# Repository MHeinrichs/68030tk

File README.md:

[This project moved to gitlab on the day M$ bought github](https://gitlab.com/MHeinrichs/68030tk)

The new repository is at: https://gitlab.com/MHeinrichs/68030tk

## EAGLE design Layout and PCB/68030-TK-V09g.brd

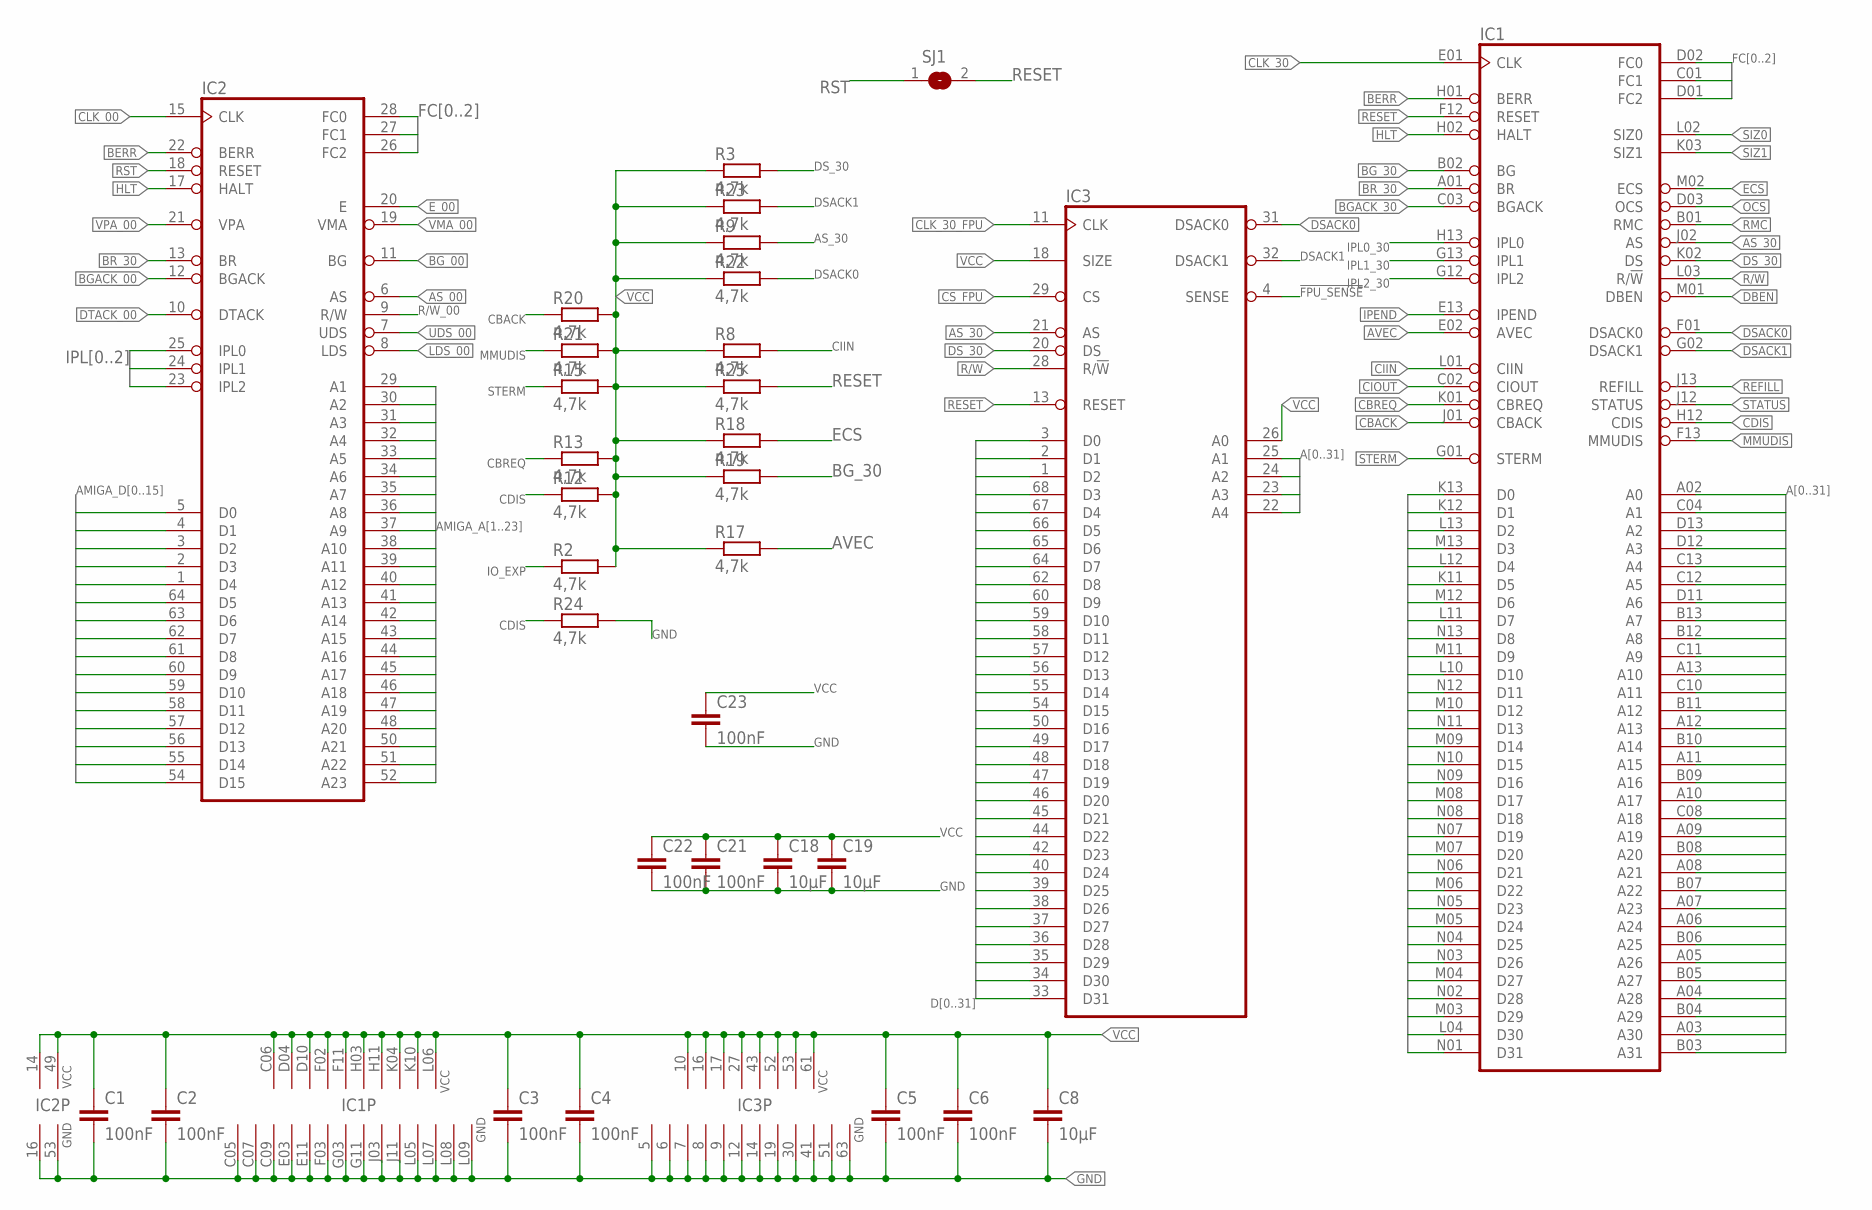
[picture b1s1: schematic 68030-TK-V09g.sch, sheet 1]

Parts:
C1, C2, C3, C4, C5, C6, C21, C22, C23: 100nF; C0603K
C8, C18, C19: 10µF; C1210
IC1: MC68030RC; MPGA128
IC2: MC68000P; DIL64
IC3: MC68881FN; PLCC68
R2, R3, R8, R9, R12, R13, R15, R17, R18, R19, R20, R21, R22, R23, R24, R25: 4,7k; R0603
SJ1: SJ

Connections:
!FPU_SENSE: IC3.4 (SENSE); also elsewhere on the board
A0: IC1.A02 (A0); also elsewhere on the board
A1: IC1.C04 (A1), IC3.25 (A1); also elsewhere on the board
A2: IC1.D13 (A2), IC3.24 (A2); also elsewhere on the board
A3: IC1.D12 (A3), IC3.23 (A3); also elsewhere on the board
A4: IC1.C13 (A4), IC3.22 (A4); also elsewhere on the board
A5: IC1.C12 (A5); also elsewhere on the board
A6: IC1.D11 (A6); also elsewhere on the board
A7: IC1.B13 (A7); also elsewhere on the board
A8: IC1.B12 (A8); also elsewhere on the board
A9: IC1.C11 (A9); also elsewhere on the board
A10: IC1.A13 (A10); also elsewhere on the board
A11: IC1.C10 (A11); also elsewhere on the board
A12: IC1.B11 (A12); also elsewhere on the board
A13: IC1.A12 (A13); also elsewhere on the board
A14: IC1.B10 (A14); also elsewhere on the board
A15: IC1.A11 (A15); also elsewhere on the board
A16: IC1.B09 (A16); also elsewhere on the board
A17: IC1.A10 (A17); also elsewhere on the board
A18: IC1.C08 (A18); also elsewhere on the board
A19: IC1.A09 (A19); also elsewhere on the board
A20: IC1.B08 (A20); also elsewhere on the board
A21: IC1.A08 (A21); also elsewhere on the board
A22: IC1.B07 (A22); also elsewhere on the board
A23: IC1.A07 (A23); also elsewhere on the board
A24: IC1.A06 (A24); also elsewhere on the board
A25: IC1.B06 (A25); also elsewhere on the board
A26: IC1.A05 (A26); also elsewhere on the board
A27: IC1.B05 (A27); also elsewhere on the board
A28: IC1.A04 (A28); also elsewhere on the board
A29: IC1.B04 (A29); also elsewhere on the board
A30: IC1.A03 (A30); also elsewhere on the board
A31: IC1.B03 (A31); also elsewhere on the board
AMIGA_A1: IC2.29 (A1); also elsewhere on the board
AMIGA_A2: IC2.30 (A2); also elsewhere on the board
AMIGA_A3: IC2.31 (A3); also elsewhere on the board
AMIGA_A4: IC2.32 (A4); also elsewhere on the board
AMIGA_A5: IC2.33 (A5); also elsewhere on the board
AMIGA_A6: IC2.34 (A6); also elsewhere on the board
AMIGA_A7: IC2.35 (A7); also elsewhere on the board
AMIGA_A8: IC2.36 (A8); also elsewhere on the board
AMIGA_A9: IC2.37 (A9); also elsewhere on the board
AMIGA_A10: IC2.38 (A10); also elsewhere on the board
AMIGA_A11: IC2.39 (A11); also elsewhere on the board
AMIGA_A12: IC2.40 (A12); also elsewhere on the board
AMIGA_A13: IC2.41 (A13); also elsewhere on the board
AMIGA_A14: IC2.42 (A14); also elsewhere on the board
AMIGA_A15: IC2.43 (A15); also elsewhere on the board
AMIGA_A16: IC2.44 (A16); also elsewhere on the board
AMIGA_A17: IC2.45 (A17); also elsewhere on the board
AMIGA_A18: IC2.46 (A18); also elsewhere on the board
AMIGA_A19: IC2.47 (A19); also elsewhere on the board
AMIGA_A20: IC2.48 (A20); also elsewhere on the board
AMIGA_A21: IC2.50 (A21); also elsewhere on the board
AMIGA_A22: IC2.51 (A22); also elsewhere on the board
AMIGA_A23: IC2.52 (A23); also elsewhere on the board
AMIGA_D0: IC2.5 (D0); also elsewhere on the board
AMIGA_D1: IC2.4 (D1); also elsewhere on the board
AMIGA_D2: IC2.3 (D2); also elsewhere on the board
AMIGA_D3: IC2.2 (D3); also elsewhere on the board
AMIGA_D4: IC2.1 (D4); also elsewhere on the board
AMIGA_D5: IC2.64 (D5); also elsewhere on the board
AMIGA_D6: IC2.63 (D6); also elsewhere on the board
AMIGA_D7: IC2.62 (D7); also elsewhere on the board
AMIGA_D8: IC2.61 (D8); also elsewhere on the board
AMIGA_D9: IC2.60 (D9); also elsewhere on the board
AMIGA_D10: IC2.59 (D10); also elsewhere on the board
AMIGA_D11: IC2.58 (D11); also elsewhere on the board
AMIGA_D12: IC2.57 (D12); also elsewhere on the board
AMIGA_D13: IC2.56 (D13); also elsewhere on the board
AMIGA_D14: IC2.55 (D14); also elsewhere on the board
AMIGA_D15: IC2.54 (D15); also elsewhere on the board
AS_00: IC2.6 (AS); also elsewhere on the board
AS_30: IC1.J02 (AS), IC3.21 (AS), R9.2; also elsewhere on the board
AVEC: IC1.E02 (AVEC), R17.2; also elsewhere on the board
BERR: IC1.H01 (BERR), IC2.22 (BERR); also elsewhere on the board
BGACK_00: IC2.12 (BGACK); also elsewhere on the board
BGACK_30: IC1.C03 (BGACK); also elsewhere on the board
BG_00: IC2.11 (BG); also elsewhere on the board
BG_30: IC1.B02 (BG), R19.2; also elsewhere on the board
BR_30: IC1.A01 (BR), IC2.13 (BR); also elsewhere on the board
CBACK: IC1.J01 (CBACK), R20.1; also elsewhere on the board
CBREQ: IC1.K01 (CBREQ), R13.1; also elsewhere on the board
CDIS: IC1.H12 (CDIS), R12.1, R24.1
CIIN: IC1.L01 (CIIN), R8.2; also elsewhere on the board
CIOUT: IC1.C02 (CIOUT)
CLK_00: IC2.15 (CLK); also elsewhere on the board
CLK_30: IC1.E01 (CLK); also elsewhere on the board
CLK_30_FPU: IC3.11 (CLK); also elsewhere on the board
CS_FPU: IC3.29 (CS); also elsewhere on the board
D0: IC1.K13 (D0), IC3.3 (D0); also elsewhere on the board
D1: IC1.K12 (D1), IC3.2 (D1); also elsewhere on the board
D2: IC1.L13 (D2), IC3.1 (D2); also elsewhere on the board
D3: IC1.M13 (D3), IC3.68 (D3); also elsewhere on the board
D4: IC1.L12 (D4), IC3.67 (D4); also elsewhere on the board
D5: IC1.K11 (D5), IC3.66 (D5); also elsewhere on the board
D6: IC1.M12 (D6), IC3.65 (D6); also elsewhere on the board
D7: IC1.L11 (D7), IC3.64 (D7); also elsewhere on the board
D8: IC1.N13 (D8), IC3.62 (D8); also elsewhere on the board
D9: IC1.M11 (D9), IC3.60 (D9); also elsewhere on the board
D10: IC1.L10 (D10), IC3.59 (D10); also elsewhere on the board
D11: IC1.N12 (D11), IC3.58 (D11); also elsewhere on the board
D12: IC1.M10 (D12), IC3.57 (D12); also elsewhere on the board
D13: IC1.N11 (D13), IC3.56 (D13); also elsewhere on the board
D14: IC1.M09 (D14), IC3.55 (D14); also elsewhere on the board
D15: IC1.N10 (D15), IC3.54 (D15); also elsewhere on the board
D16: IC1.N09 (D16), IC3.50 (D16); also elsewhere on the board
D17: IC1.M08 (D17), IC3.49 (D17); also elsewhere on the board
D18: IC1.N08 (D18), IC3.48 (D18); also elsewhere on the board
D19: IC1.N07 (D19), IC3.47 (D19); also elsewhere on the board
D20: IC1.M07 (D20), IC3.46 (D20); also elsewhere on the board
D21: IC1.N06 (D21), IC3.45 (D21); also elsewhere on the board
D22: IC1.M06 (D22), IC3.44 (D22); also elsewhere on the board
D23: IC1.N05 (D23), IC3.42 (D23); also elsewhere on the board
D24: IC1.M05 (D24), IC3.40 (D24); also elsewhere on the board
D25: IC1.N04 (D25), IC3.39 (D25); also elsewhere on the board
D26: IC1.N03 (D26), IC3.38 (D26); also elsewhere on the board
D27: IC1.M04 (D27), IC3.37 (D27); also elsewhere on the board
D28: IC1.N02 (D28), IC3.36 (D28); also elsewhere on the board
D29: IC1.M03 (D29), IC3.35 (D29); also elsewhere on the board
D30: IC1.L04 (D30), IC3.34 (D30); also elsewhere on the board
D31: IC1.N01 (D31), IC3.33 (D31); also elsewhere on the board
DBEN: IC1.M01 (DBEN)
DSACK0: IC1.F01 (DSACK0), IC3.31 (DSACK0), R22.2; also elsewhere on the board
DSACK1: IC1.G02 (DSACK1), IC3.32 (DSACK1), R23.2; also elsewhere on the board
DS_30: IC1.K02 (DS), IC3.20 (DS), R3.2; also elsewhere on the board
DTACK_00: IC2.10 (DTACK); also elsewhere on the board
ECS: IC1.M02 (ECS), R18.2; also elsewhere on the board
E_00: IC2.20 (E); also elsewhere on the board
FC0: IC1.D02 (FC0), IC2.28 (FC0); also elsewhere on the board
FC1: IC1.C01 (FC1), IC2.27 (FC1); also elsewhere on the board
FC2: IC1.D01 (FC2), IC2.26 (FC2); also elsewhere on the board
GND: C1.2, C2.2, C3.2, C4.2, C5.2, C6.2, C8.2, C18.2, C19.2, C21.2, C22.2, C23.2, IC1.C05 (GND), IC1.C07 (GND), IC1.C09 (GND), IC1.E03 (GND), IC1.E11 (GND), IC1.F03 (GND), IC1.G03 (GND), IC1.G11 (GND), IC1.J03 (GND), IC1.J11 (GND), IC1.L05 (GND), IC1.L07 (GND), IC1.L08 (GND), IC1.L09 (GND), IC2.16 (GND), IC2.53 (GND), IC3.5 (GND), IC3.6 (GND), IC3.7 (GND), IC3.8 (GND), IC3.9 (GND), IC3.12 (GND), IC3.14 (GND), IC3.19 (GND), IC3.30 (GND), IC3.41 (GND), IC3.51 (GND), IC3.63 (GND), R24.2; also elsewhere on the board
HLT: IC1.H02 (HALT), IC2.17 (HALT)
IO_EXP: R2.1; also elsewhere on the board
IPEND: IC1.E13 (IPEND)
IPL0: IC2.25 (IPL0); also elsewhere on the board
IPL0_30: IC1.H13 (IPL0); also elsewhere on the board
IPL1: IC2.24 (IPL1); also elsewhere on the board
IPL1_30: IC1.G13 (IPL1); also elsewhere on the board
IPL2: IC2.23 (IPL2); also elsewhere on the board
IPL2_30: IC1.G12 (IPL2); also elsewhere on the board
LDS_00: IC2.8 (LDS); also elsewhere on the board
MMUDIS: IC1.F13 (MMUDIS), R21.1
OCS: IC1.D03 (OCS)
R/W: IC1.L03 (R/!W), IC3.28 (R/!W); also elsewhere on the board
R/W_00: IC2.9 (R/W); also elsewhere on the board
REFILL: IC1.J13 (REFILL)
RESET: IC1.F12 (RESET), IC3.13 (RESET), R25.2, SJ1.2; also elsewhere on the board
RMC: IC1.B01 (RMC)
RST: IC2.18 (RESET), SJ1.1; also elsewhere on the board
SIZ0: IC1.L02 (SIZ0); also elsewhere on the board
SIZ1: IC1.K03 (SIZ1); also elsewhere on the board
STATUS: IC1.J12 (STATUS)
STERM: IC1.G01 (STERM), R15.1; also elsewhere on the board
UDS_00: IC2.7 (UDS); also elsewhere on the board
VCC: C1.1, C2.1, C3.1, C4.1, C5.1, C6.1, C8.1, C18.1, C19.1, C21.1, C22.1, C23.1, IC1.C06 (VCC), IC1.D04 (VCC), IC1.D10 (VCC), IC1.F02 (VCC), IC1.F11 (VCC), IC1.H03 (VCC), IC1.H11 (VCC), IC1.K04 (VCC), IC1.K10 (VCC), IC1.L06 (VCC), IC2.14 (VCC), IC2.49 (VCC), IC3.10 (VCC), IC3.16 (VCC), IC3.17 (VCC), IC3.18 (SIZE), IC3.26 (A0), IC3.27 (VCC), IC3.43 (VCC), IC3.52 (VCC), IC3.53 (VCC), IC3.61 (VCC), R2.2, R3.1, R8.1, R9.1, R12.2, R13.2, R15.2, R17.1, R18.1, R19.1, R20.2, R21.2, R22.1, R23.1, R25.1; also elsewhere on the board
VMA_00: IC2.19 (VMA); also elsewhere on the board
VPA_00: IC2.21 (VPA); also elsewhere on the board

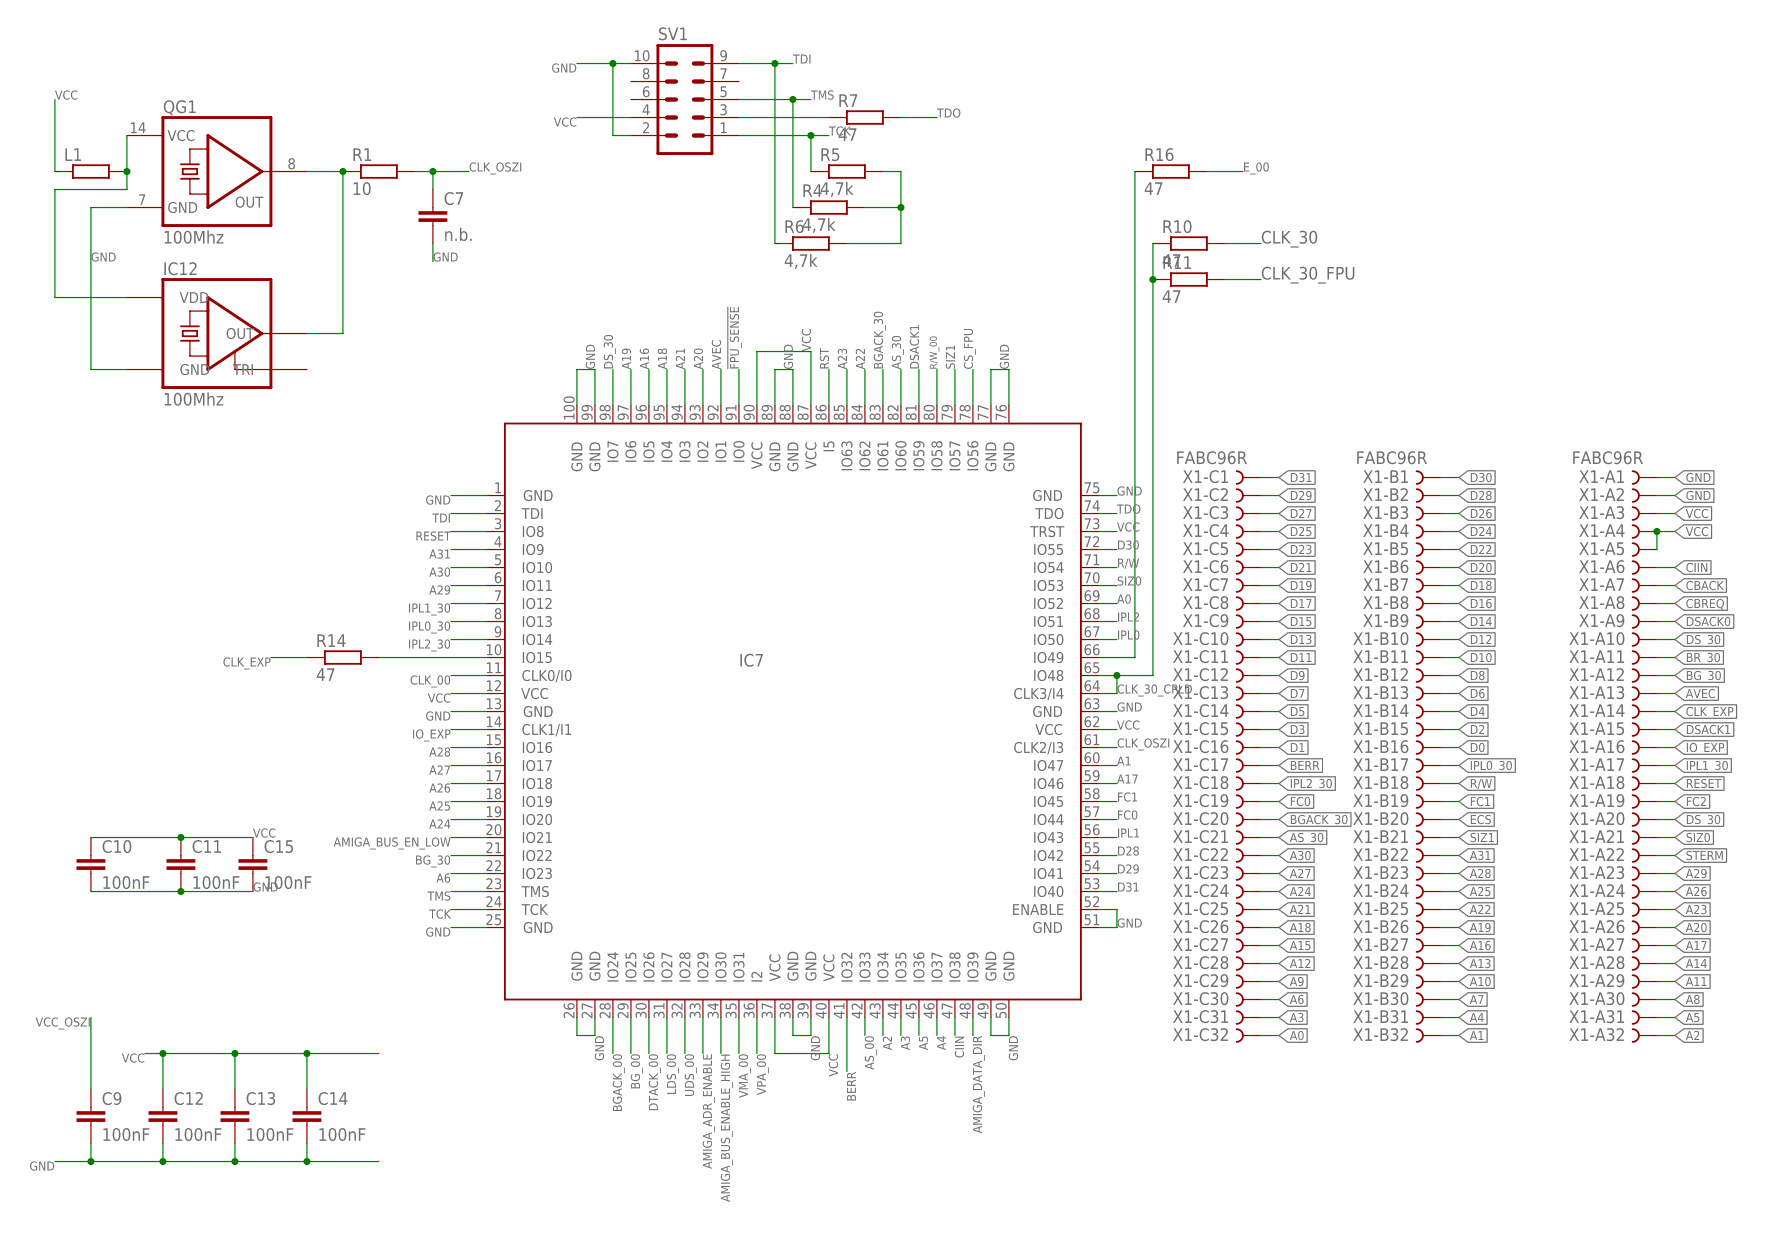
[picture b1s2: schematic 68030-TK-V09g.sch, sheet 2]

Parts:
C7: n.b.; C0805K
C9, C10, C11, C12, C13, C14, C15: 100nF; C0603K
IC7: M4-128T100; TQFP100
IC12: 100Mhz; 7X5
L1: R-EU_R0805; R0805
QG1: 100Mhz; DIL14S
R1: 10; R0805
R4, R5, R6: 4,7k; R0603
R7, R10, R11, R14, R16: 47; R0603
SV1: ML10
X1: FABC96R

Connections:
!FPU_SENSE: IC7.91 (IO0); also elsewhere on the board
A0: IC7.69 (IO52), X1.C32; also elsewhere on the board
A1: IC7.60 (IO47), X1.B32; also elsewhere on the board
A2: IC7.43 (IO34), X1.A32; also elsewhere on the board
A3: IC7.44 (IO35), X1.C31; also elsewhere on the board
A4: IC7.46 (IO37), X1.B31; also elsewhere on the board
A5: IC7.45 (IO36), X1.A31; also elsewhere on the board
A6: IC7.22 (IO23), X1.C30; also elsewhere on the board
A7: X1.B30; also elsewhere on the board
A8: X1.A30; also elsewhere on the board
A9: X1.C29; also elsewhere on the board
A10: X1.B29; also elsewhere on the board
A11: X1.A29; also elsewhere on the board
A12: X1.C28; also elsewhere on the board
A13: X1.B28; also elsewhere on the board
A14: X1.A28; also elsewhere on the board
A15: X1.C27; also elsewhere on the board
A16: IC7.96 (IO5), X1.B27; also elsewhere on the board
A17: IC7.59 (IO46), X1.A27; also elsewhere on the board
A18: IC7.95 (IO4), X1.C26; also elsewhere on the board
A19: IC7.97 (IO6), X1.B26; also elsewhere on the board
A20: IC7.93 (IO2), X1.A26; also elsewhere on the board
A21: IC7.94 (IO3), X1.C25; also elsewhere on the board
A22: IC7.84 (IO62), X1.B25; also elsewhere on the board
A23: IC7.85 (IO63), X1.A25; also elsewhere on the board
A24: IC7.19 (IO20), X1.C24; also elsewhere on the board
A25: IC7.18 (IO19), X1.B24; also elsewhere on the board
A26: IC7.17 (IO18), X1.A24; also elsewhere on the board
A27: IC7.16 (IO17), X1.C23; also elsewhere on the board
A28: IC7.15 (IO16), X1.B23; also elsewhere on the board
A29: IC7.6 (IO11), X1.A23; also elsewhere on the board
A30: IC7.5 (IO10), X1.C22; also elsewhere on the board
A31: IC7.4 (IO9), X1.B22; also elsewhere on the board
AMIGA_ADR_ENABLE: IC7.33 (IO29); also elsewhere on the board
AMIGA_BUS_ENABLE_HIGH: IC7.34 (IO30); also elsewhere on the board
AMIGA_BUS_EN_LOW: IC7.20 (IO21); also elsewhere on the board
AMIGA_DATA_DIR: IC7.48 (IO39); also elsewhere on the board
AS_00: IC7.42 (IO33); also elsewhere on the board
AS_30: IC7.82 (IO60), X1.C21; also elsewhere on the board
AVEC: IC7.92 (IO1), X1.A13; also elsewhere on the board
BERR: IC7.41 (IO32), X1.C17; also elsewhere on the board
BGACK_00: IC7.28 (IO24); also elsewhere on the board
BGACK_30: IC7.83 (IO61), X1.C20; also elsewhere on the board
BG_00: IC7.29 (IO25); also elsewhere on the board
BG_30: IC7.21 (IO22), X1.A12; also elsewhere on the board
BR_30: X1.A11; also elsewhere on the board
CBACK: X1.A7; also elsewhere on the board
CBREQ: X1.A8; also elsewhere on the board
CIIN: IC7.47 (IO38), X1.A6; also elsewhere on the board
CLK_00: IC7.11 (CLK0/I0); also elsewhere on the board
CLK_30: R10.2; also elsewhere on the board
CLK_30_CPLD: IC7.64 (CLK3/I4), IC7.65 (IO48), R10.1, R11.1
CLK_30_FPU: R11.2; also elsewhere on the board
CLK_EXP: R14.1, X1.A14
CLK_OSZI: C7.1, IC7.61 (CLK2/I3), R1.2
CS_FPU: IC7.78 (IO56); also elsewhere on the board
D0: X1.B16; also elsewhere on the board
D1: X1.C16; also elsewhere on the board
D2: X1.B15; also elsewhere on the board
D3: X1.C15; also elsewhere on the board
D4: X1.B14; also elsewhere on the board
D5: X1.C14; also elsewhere on the board
D6: X1.B13; also elsewhere on the board
D7: X1.C13; also elsewhere on the board
D8: X1.B12; also elsewhere on the board
D9: X1.C12; also elsewhere on the board
D10: X1.B11; also elsewhere on the board
D11: X1.C11; also elsewhere on the board
D12: X1.B10; also elsewhere on the board
D13: X1.C10; also elsewhere on the board
D14: X1.B9; also elsewhere on the board
D15: X1.C9; also elsewhere on the board
D16: X1.B8; also elsewhere on the board
D17: X1.C8; also elsewhere on the board
D18: X1.B7; also elsewhere on the board
D19: X1.C7; also elsewhere on the board
D20: X1.B6; also elsewhere on the board
D21: X1.C6; also elsewhere on the board
D22: X1.B5; also elsewhere on the board
D23: X1.C5; also elsewhere on the board
D24: X1.B4; also elsewhere on the board
D25: X1.C4; also elsewhere on the board
D26: X1.B3; also elsewhere on the board
D27: X1.C3; also elsewhere on the board
D28: IC7.55 (IO42), X1.B2; also elsewhere on the board
D29: IC7.54 (IO41), X1.C2; also elsewhere on the board
D30: IC7.72 (IO55), X1.B1; also elsewhere on the board
D31: IC7.53 (IO40), X1.C1; also elsewhere on the board
DSACK0: X1.A9; also elsewhere on the board
DSACK1: IC7.81 (IO59), X1.A15; also elsewhere on the board
DS_30: IC7.98 (IO7), X1.A10, X1.A20; also elsewhere on the board
DTACK_00: IC7.30 (IO26); also elsewhere on the board
ECS: X1.B20; also elsewhere on the board
E_00: R16.2; also elsewhere on the board
FC0: IC7.57 (IO44), X1.C19; also elsewhere on the board
FC1: IC7.58 (IO45), X1.B19; also elsewhere on the board
FC2: X1.A19; also elsewhere on the board
GND: C7.2, C9.2, C10.2, C11.2, C12.2, C13.2, C14.2, C15.2, IC7.1 (GND), IC7.13 (GND), IC7.25 (GND), IC7.26 (GND), IC7.27 (GND), IC7.38 (GND), IC7.39 (GND), IC7.49 (GND), IC7.50 (GND), IC7.51 (GND), IC7.52 (ENABLE), IC7.63 (GND), IC7.75 (GND), IC7.76 (GND), IC7.77 (GND), IC7.88 (GND), IC7.89 (GND), IC7.99 (GND), IC7.100 (GND), IC12.P$2 (GND), QG1.7 (GND), SV1.2, SV1.10, X1.A1, X1.A2; also elsewhere on the board
IO_EXP: IC7.14 (CLK1/I1), X1.A16; also elsewhere on the board
IPL0: IC7.67 (IO50); also elsewhere on the board
IPL0_30: IC7.8 (IO13), X1.B17; also elsewhere on the board
IPL1: IC7.56 (IO43); also elsewhere on the board
IPL1_30: IC7.7 (IO12), X1.A17; also elsewhere on the board
IPL2: IC7.68 (IO51); also elsewhere on the board
IPL2_30: IC7.9 (IO14), X1.C18; also elsewhere on the board
LDS_00: IC7.31 (IO27); also elsewhere on the board
unnamed: IC7.10 (IO15), R14.2
unnamed: IC7.66 (IO49), R16.1
OSZI_OUT: IC12.P$3 (OUT), QG1.8 (OUT), R1.1
R/W: IC7.71 (IO54), X1.B18; also elsewhere on the board
R/W_00: IC7.80 (IO58); also elsewhere on the board
RESET: IC7.3 (IO8), X1.A18; also elsewhere on the board
RST: IC7.86 (I5); also elsewhere on the board
SIZ0: IC7.70 (IO53), X1.A21; also elsewhere on the board
SIZ1: IC7.79 (IO57), X1.B21; also elsewhere on the board
STERM: X1.A22; also elsewhere on the board
TCK: IC7.24 (TCK), R5.1, SV1.1
TDI: IC7.2 (TDI), R6.1, SV1.9
TDO: IC7.74 (TDO), R7.2
TDO-PIN: R7.1, SV1.3
TMS: IC7.23 (TMS), R4.1, SV1.5
UDS_00: IC7.32 (IO28); also elsewhere on the board
VCC: C10.1, C11.1, C12.1, C13.1, C14.1, C15.1, IC7.12 (VCC), IC7.37 (VCC), IC7.40 (VCC), IC7.62 (VCC), IC7.73 (TRST), IC7.87 (VCC), IC7.90 (VCC), L1.1, R4.2, R5.2, R6.2, SV1.4, X1.A3, X1.A4, X1.A5; also elsewhere on the board
VCC_OSZI: C9.1, IC12.P$4 (VDD), L1.2, QG1.14 (VCC)
VMA_00: IC7.35 (IO31); also elsewhere on the board
VPA_00: IC7.36 (I2); also elsewhere on the board

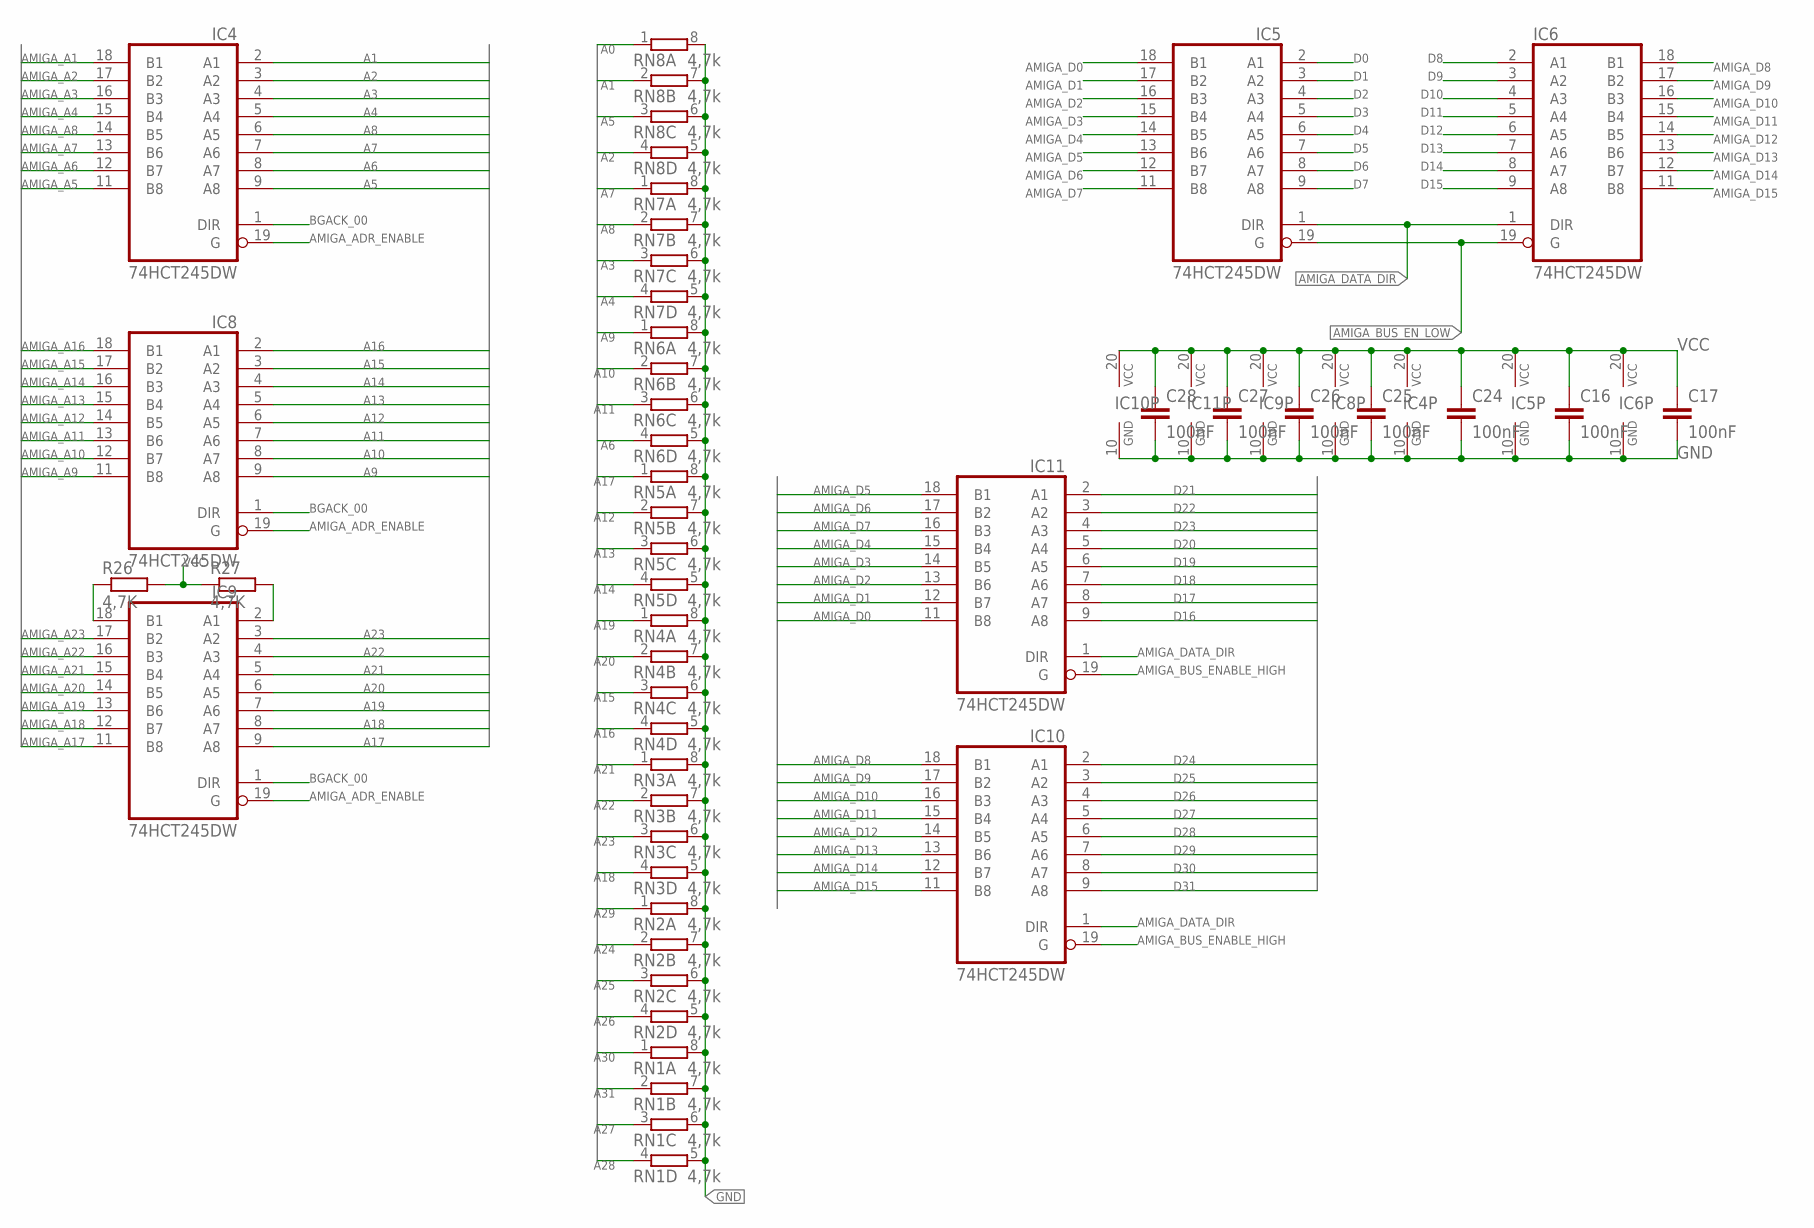
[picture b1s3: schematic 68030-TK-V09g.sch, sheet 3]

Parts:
C16, C17, C24, C25, C26, C27, C28: 100nF; C0603K
IC4, IC5, IC6, IC8, IC9, IC10, IC11: 74HCT245DW; SO20W
R26, R27: 4,7K; R0603
RN1, RN2, RN3, RN4, RN5, RN6, RN7, RN8: 4,7k; EXBV8V

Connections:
A0: RN8.1; also elsewhere on the board
A1: IC4.2 (A1), RN8.2 (1); also elsewhere on the board
A2: IC4.3 (A2), RN8.4 (1); also elsewhere on the board
A3: IC4.4 (A3), RN7.3 (1); also elsewhere on the board
A4: IC4.5 (A4), RN7.4 (1); also elsewhere on the board
A5: IC4.9 (A8), RN8.3 (1); also elsewhere on the board
A6: IC4.8 (A7), RN6.4 (1); also elsewhere on the board
A7: IC4.7 (A6), RN7.1; also elsewhere on the board
A8: IC4.6 (A5), RN7.2 (1); also elsewhere on the board
A9: IC8.9 (A8), RN6.1; also elsewhere on the board
A10: IC8.8 (A7), RN6.2 (1); also elsewhere on the board
A11: IC8.7 (A6), RN6.3 (1); also elsewhere on the board
A12: IC8.6 (A5), RN5.2 (1); also elsewhere on the board
A13: IC8.5 (A4), RN5.3 (1); also elsewhere on the board
A14: IC8.4 (A3), RN5.4 (1); also elsewhere on the board
A15: IC8.3 (A2), RN4.3 (1); also elsewhere on the board
A16: IC8.2 (A1), RN4.4 (1); also elsewhere on the board
A17: IC9.9 (A8), RN5.1; also elsewhere on the board
A18: IC9.8 (A7), RN3.4 (1); also elsewhere on the board
A19: IC9.7 (A6), RN4.1; also elsewhere on the board
A20: IC9.6 (A5), RN4.2 (1); also elsewhere on the board
A21: IC9.5 (A4), RN3.1; also elsewhere on the board
A22: IC9.4 (A3), RN3.2 (1); also elsewhere on the board
A23: IC9.3 (A2), RN3.3 (1); also elsewhere on the board
A24: RN2.2 (1); also elsewhere on the board
A25: RN2.3 (1); also elsewhere on the board
A26: RN2.4 (1); also elsewhere on the board
A27: RN1.3 (1); also elsewhere on the board
A28: RN1.4 (1); also elsewhere on the board
A29: RN2.1; also elsewhere on the board
A30: RN1.1; also elsewhere on the board
A31: RN1.2 (1); also elsewhere on the board
AMIGA_A1: IC4.18 (B1); also elsewhere on the board
AMIGA_A2: IC4.17 (B2); also elsewhere on the board
AMIGA_A3: IC4.16 (B3); also elsewhere on the board
AMIGA_A4: IC4.15 (B4); also elsewhere on the board
AMIGA_A5: IC4.11 (B8); also elsewhere on the board
AMIGA_A6: IC4.12 (B7); also elsewhere on the board
AMIGA_A7: IC4.13 (B6); also elsewhere on the board
AMIGA_A8: IC4.14 (B5); also elsewhere on the board
AMIGA_A9: IC8.11 (B8); also elsewhere on the board
AMIGA_A10: IC8.12 (B7); also elsewhere on the board
AMIGA_A11: IC8.13 (B6); also elsewhere on the board
AMIGA_A12: IC8.14 (B5); also elsewhere on the board
AMIGA_A13: IC8.15 (B4); also elsewhere on the board
AMIGA_A14: IC8.16 (B3); also elsewhere on the board
AMIGA_A15: IC8.17 (B2); also elsewhere on the board
AMIGA_A16: IC8.18 (B1); also elsewhere on the board
AMIGA_A17: IC9.11 (B8); also elsewhere on the board
AMIGA_A18: IC9.12 (B7); also elsewhere on the board
AMIGA_A19: IC9.13 (B6); also elsewhere on the board
AMIGA_A20: IC9.14 (B5); also elsewhere on the board
AMIGA_A21: IC9.15 (B4); also elsewhere on the board
AMIGA_A22: IC9.16 (B3); also elsewhere on the board
AMIGA_A23: IC9.17 (B2); also elsewhere on the board
AMIGA_ADR_ENABLE: IC4.19 (G), IC8.19 (G), IC9.19 (G); also elsewhere on the board
AMIGA_BUS_ENABLE_HIGH: IC10.19 (G), IC11.19 (G); also elsewhere on the board
AMIGA_BUS_EN_LOW: IC5.19 (G), IC6.19 (G); also elsewhere on the board
AMIGA_D0: IC5.18 (B1), IC11.11 (B8); also elsewhere on the board
AMIGA_D1: IC5.17 (B2), IC11.12 (B7); also elsewhere on the board
AMIGA_D2: IC5.16 (B3), IC11.13 (B6); also elsewhere on the board
AMIGA_D3: IC5.15 (B4), IC11.14 (B5); also elsewhere on the board
AMIGA_D4: IC5.14 (B5), IC11.15 (B4); also elsewhere on the board
AMIGA_D5: IC5.13 (B6), IC11.18 (B1); also elsewhere on the board
AMIGA_D6: IC5.12 (B7), IC11.17 (B2); also elsewhere on the board
AMIGA_D7: IC5.11 (B8), IC11.16 (B3); also elsewhere on the board
AMIGA_D8: IC6.18 (B1), IC10.18 (B1); also elsewhere on the board
AMIGA_D9: IC6.17 (B2), IC10.17 (B2); also elsewhere on the board
AMIGA_D10: IC6.16 (B3), IC10.16 (B3); also elsewhere on the board
AMIGA_D11: IC6.15 (B4), IC10.15 (B4); also elsewhere on the board
AMIGA_D12: IC6.14 (B5), IC10.14 (B5); also elsewhere on the board
AMIGA_D13: IC6.13 (B6), IC10.13 (B6); also elsewhere on the board
AMIGA_D14: IC6.12 (B7), IC10.12 (B7); also elsewhere on the board
AMIGA_D15: IC6.11 (B8), IC10.11 (B8); also elsewhere on the board
AMIGA_DATA_DIR: IC5.1 (DIR), IC6.1 (DIR), IC10.1 (DIR), IC11.1 (DIR); also elsewhere on the board
BGACK_00: IC4.1 (DIR), IC8.1 (DIR), IC9.1 (DIR); also elsewhere on the board
D0: IC5.2 (A1); also elsewhere on the board
D1: IC5.3 (A2); also elsewhere on the board
D2: IC5.4 (A3); also elsewhere on the board
D3: IC5.5 (A4); also elsewhere on the board
D4: IC5.6 (A5); also elsewhere on the board
D5: IC5.7 (A6); also elsewhere on the board
D6: IC5.8 (A7); also elsewhere on the board
D7: IC5.9 (A8); also elsewhere on the board
D8: IC6.2 (A1); also elsewhere on the board
D9: IC6.3 (A2); also elsewhere on the board
D10: IC6.4 (A3); also elsewhere on the board
D11: IC6.5 (A4); also elsewhere on the board
D12: IC6.6 (A5); also elsewhere on the board
D13: IC6.7 (A6); also elsewhere on the board
D14: IC6.8 (A7); also elsewhere on the board
D15: IC6.9 (A8); also elsewhere on the board
D16: IC11.9 (A8); also elsewhere on the board
D17: IC11.8 (A7); also elsewhere on the board
D18: IC11.7 (A6); also elsewhere on the board
D19: IC11.6 (A5); also elsewhere on the board
D20: IC11.5 (A4); also elsewhere on the board
D21: IC11.2 (A1); also elsewhere on the board
D22: IC11.3 (A2); also elsewhere on the board
D23: IC11.4 (A3); also elsewhere on the board
D24: IC10.2 (A1); also elsewhere on the board
D25: IC10.3 (A2); also elsewhere on the board
D26: IC10.4 (A3); also elsewhere on the board
D27: IC10.5 (A4); also elsewhere on the board
D28: IC10.6 (A5); also elsewhere on the board
D29: IC10.7 (A6); also elsewhere on the board
D30: IC10.8 (A7); also elsewhere on the board
D31: IC10.9 (A8); also elsewhere on the board
GND: C16.2, C17.2, C24.2, C25.2, C26.2, C27.2, C28.2, IC4.10 (GND), IC5.10 (GND), IC6.10 (GND), IC8.10 (GND), IC9.10 (GND), IC10.10 (GND), IC11.10 (GND), RN1.5 (2), RN1.6 (2), RN1.7 (2), RN1.8 (2), RN2.5 (2), RN2.6 (2), RN2.7 (2), RN2.8 (2), RN3.5 (2), RN3.6 (2), RN3.7 (2), RN3.8 (2), RN4.5 (2), RN4.6 (2), RN4.7 (2), RN4.8 (2), RN5.5 (2), RN5.6 (2), RN5.7 (2), RN5.8 (2), RN6.5 (2), RN6.6 (2), RN6.7 (2), RN6.8 (2), RN7.5 (2), RN7.6 (2), RN7.7 (2), RN7.8 (2), RN8.5 (2), RN8.6 (2), RN8.7 (2), RN8.8 (2); also elsewhere on the board
unnamed: IC9.18 (B1), R26.1
unnamed: IC9.2 (A1), R27.2
VCC: C16.1, C17.1, C24.1, C25.1, C26.1, C27.1, C28.1, IC4.20 (VCC), IC5.20 (VCC), IC6.20 (VCC), IC8.20 (VCC), IC9.20 (VCC), IC10.20 (VCC), IC11.20 (VCC), R26.2, R27.1; also elsewhere on the board

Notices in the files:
Layout and PCB/68030-TK-V09g.brd:
(c) 2014 Matthias Heinrichs
(c)2013 Matthias Heinrichs
